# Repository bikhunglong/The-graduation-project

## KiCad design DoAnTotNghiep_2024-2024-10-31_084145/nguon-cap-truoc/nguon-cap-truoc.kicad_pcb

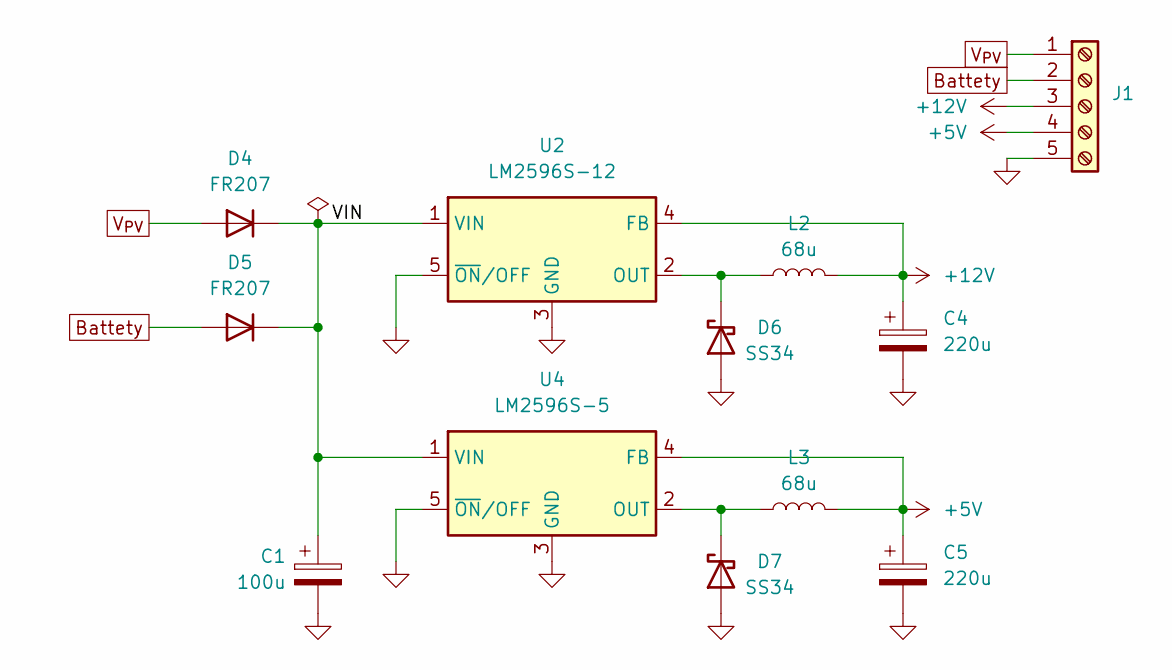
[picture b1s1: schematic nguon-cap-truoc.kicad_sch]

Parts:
C1: 100u; CP_Elec_6.3x5.4
C4, C5: 220u; CP_Elec_6.3x5.4
D4, D5: FR207; D_SMA
D6, D7: SS34; D_SMA
J1: Screw_Terminal_01x05; PinHeader_1x05_P2.54mm_Horizontal
L2, L3: 68u; L_12x12mm_H8mm
U2: LM2596S-12; TO-263-5_TabPin3
U4: LM2596S-5; TO-263-5_TabPin3

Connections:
+5V: C5.1, J1.4, L3.2, U4.4 (FB)
+12V: C4.1, J1.3, L2.2, U2.4 (FB)
/VIN: C1.1, D4.1 (K), D5.1 (K), U2.1 (VIN), U4.1 (VIN)
Battety: D5.2 (A), J1.2
GND: C1.2, C4.2, C5.2, D6.2 (A), D7.2 (A), J1.5, U2.3 (GND), U2.5 (~ON/OFF), U4.3 (GND), U4.5 (~ON/OFF)
unnamed: D6.1 (K), L2.1, U2.2 (OUT)
unnamed: D7.1 (K), L3.1, U4.2 (OUT)
V_{PV}: D4.2 (A), J1.1

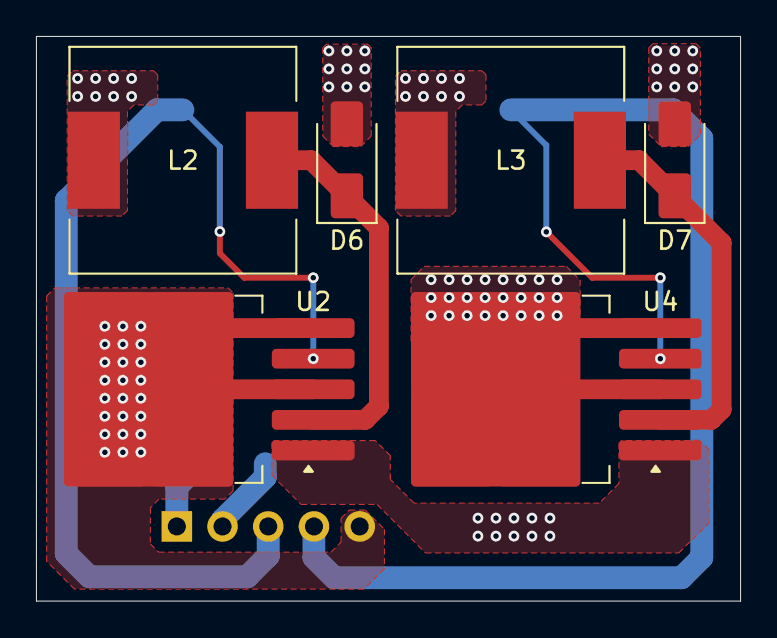
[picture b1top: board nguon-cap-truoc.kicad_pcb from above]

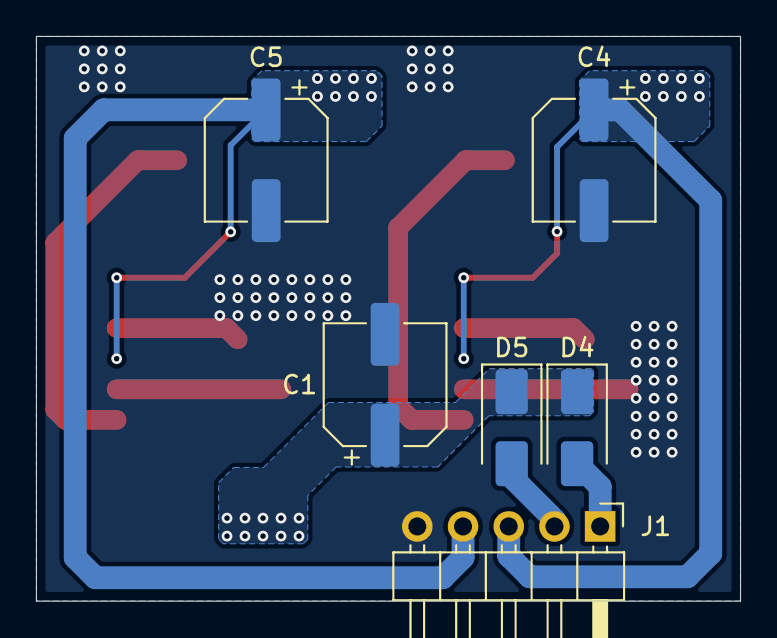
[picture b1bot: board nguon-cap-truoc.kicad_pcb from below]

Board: 2 copper layers, 39.1 x 31.4 mm, 12 parts (6 on the bottom side), 8 nets.

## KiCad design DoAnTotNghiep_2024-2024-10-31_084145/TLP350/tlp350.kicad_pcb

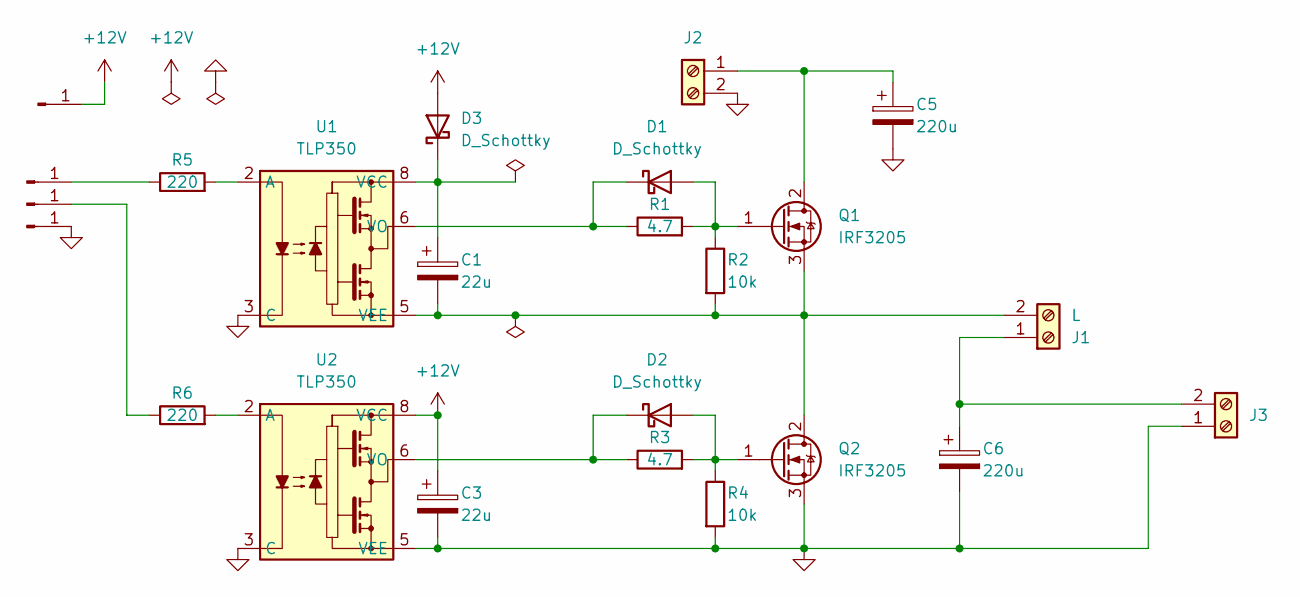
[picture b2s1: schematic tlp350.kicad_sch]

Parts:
C1, C3: 22u; CP_Radial_Tantal_D5.5mm_P5.00mm
C5, C6: 220u; CP_Radial_D10.0mm_P3.50mm
D1, D2, D3: D_Schottky; D_DO-41_SOD81_P10.16mm_Horizontal
J1, J3: L; TerminalBlock_Phoenix_MKDS-1,5-2-5.08_1x02_P5.08mm_Horizont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
J2: Screw_Terminal_01x02; TerminalBlock_Phoenix_MKDS-1,5-2-5.08_1x02_P5.08mm_Horizont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
J4, J5, J6, J7: Conn_01x01_Pin; Pin_D1.0mm_L10.0mm_LooseFit
Q1, Q2: IRF3205; TO-220-3_Vertical
R1, R3: 4.7; R_Axial_DIN0207_L6.3mm_D2.5mm_P10.16mm_Horizontal
R2, R4: 10k; R_Axial_DIN0207_L6.3mm_D2.5mm_P10.16mm_Horizontal
R5, R6: 220; R_Axial_DIN0207_L6.3mm_D2.5mm_P10.16mm_Horizontal
U1, U2: TLP350; DIP-8_W7.62mm

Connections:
+12V: C3.1, D3.2 (A), J7.1, U2.8 (VCC)
GND: C3.2, C5.2, C6.2, J2.2, J3.1, J6.1, Q2.3 (S), R4.2, U1.3 (C), U2.3 (C), U2.5 (VEE)
unnamed: D1.2 (A), Q1.1 (G), R1.2, R2.1
unnamed: D1.1 (K), R1.1, U1.6 (VO)
unnamed: D2.2 (A), Q2.1 (G), R3.2, R4.1
unnamed: D2.1 (K), R3.1, U2.6 (VO)
unnamed: C1.1, D3.1 (K), U1.8 (VCC)
unnamed: C6.1, J1.1, J3.2
unnamed: C1.2, J1.2, Q1.3 (S), Q2.2 (D), R2.2, U1.5 (VEE)
unnamed: C5.1, J2.1, Q1.2 (D)
unnamed: J4.1, R5.1
unnamed: J5.1, R6.1
unnamed: R5.2, U1.2 (A)
unnamed: R6.2, U2.2 (A)

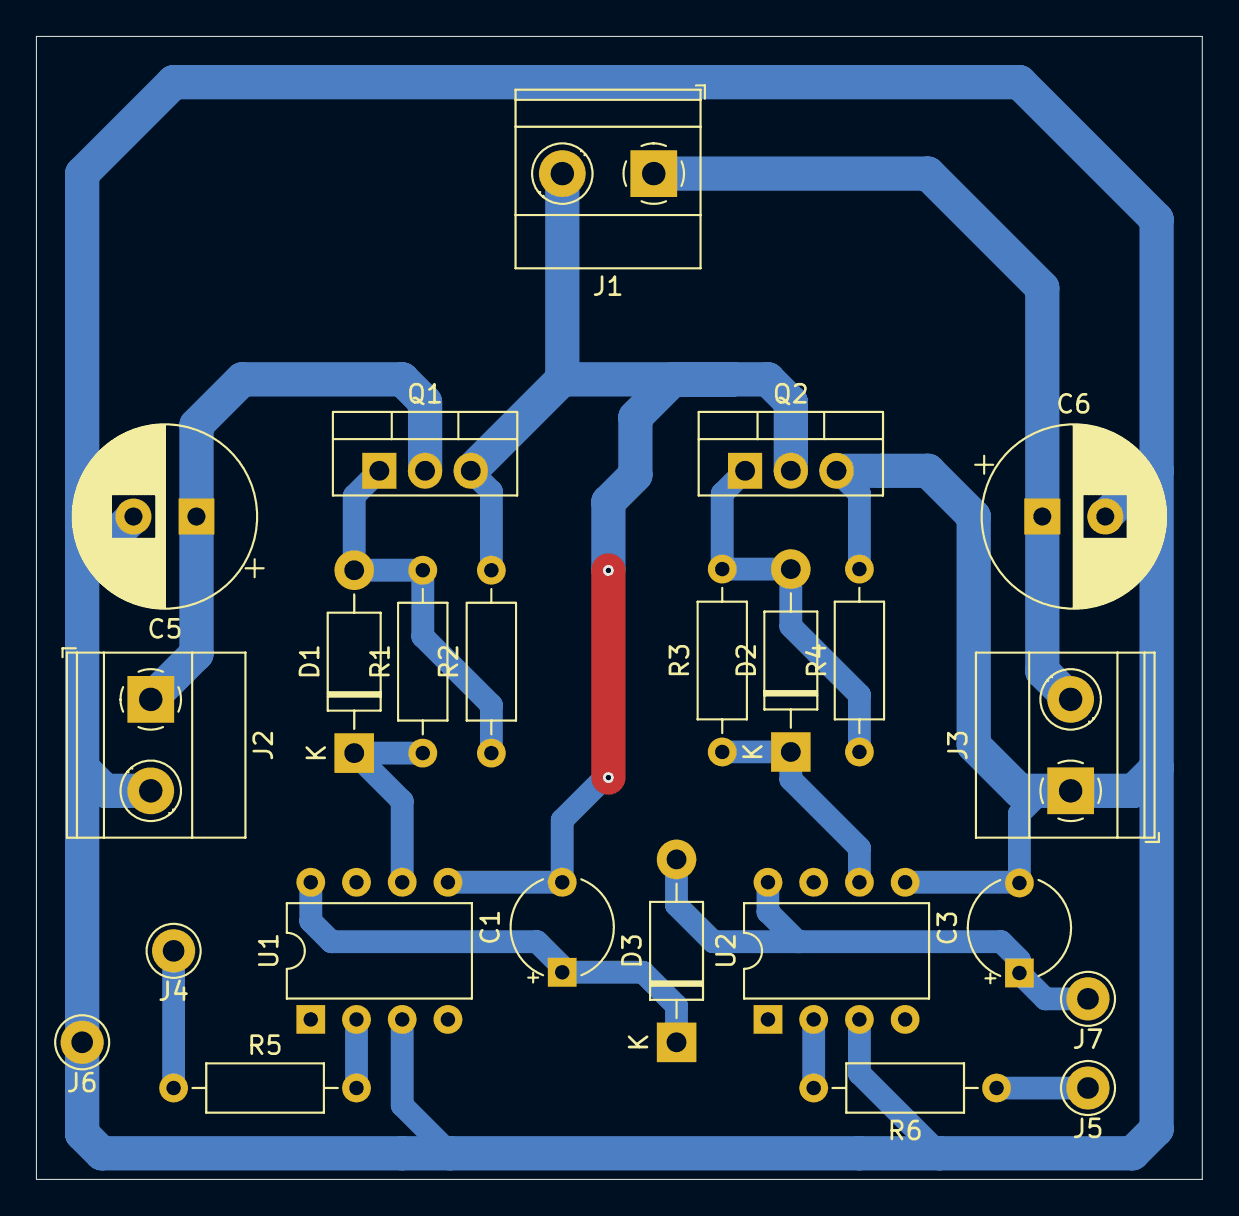
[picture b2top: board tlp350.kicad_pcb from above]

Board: 2 copper layers, 64.8 x 63.5 mm, 24 parts (0 on the bottom side), 14 nets.

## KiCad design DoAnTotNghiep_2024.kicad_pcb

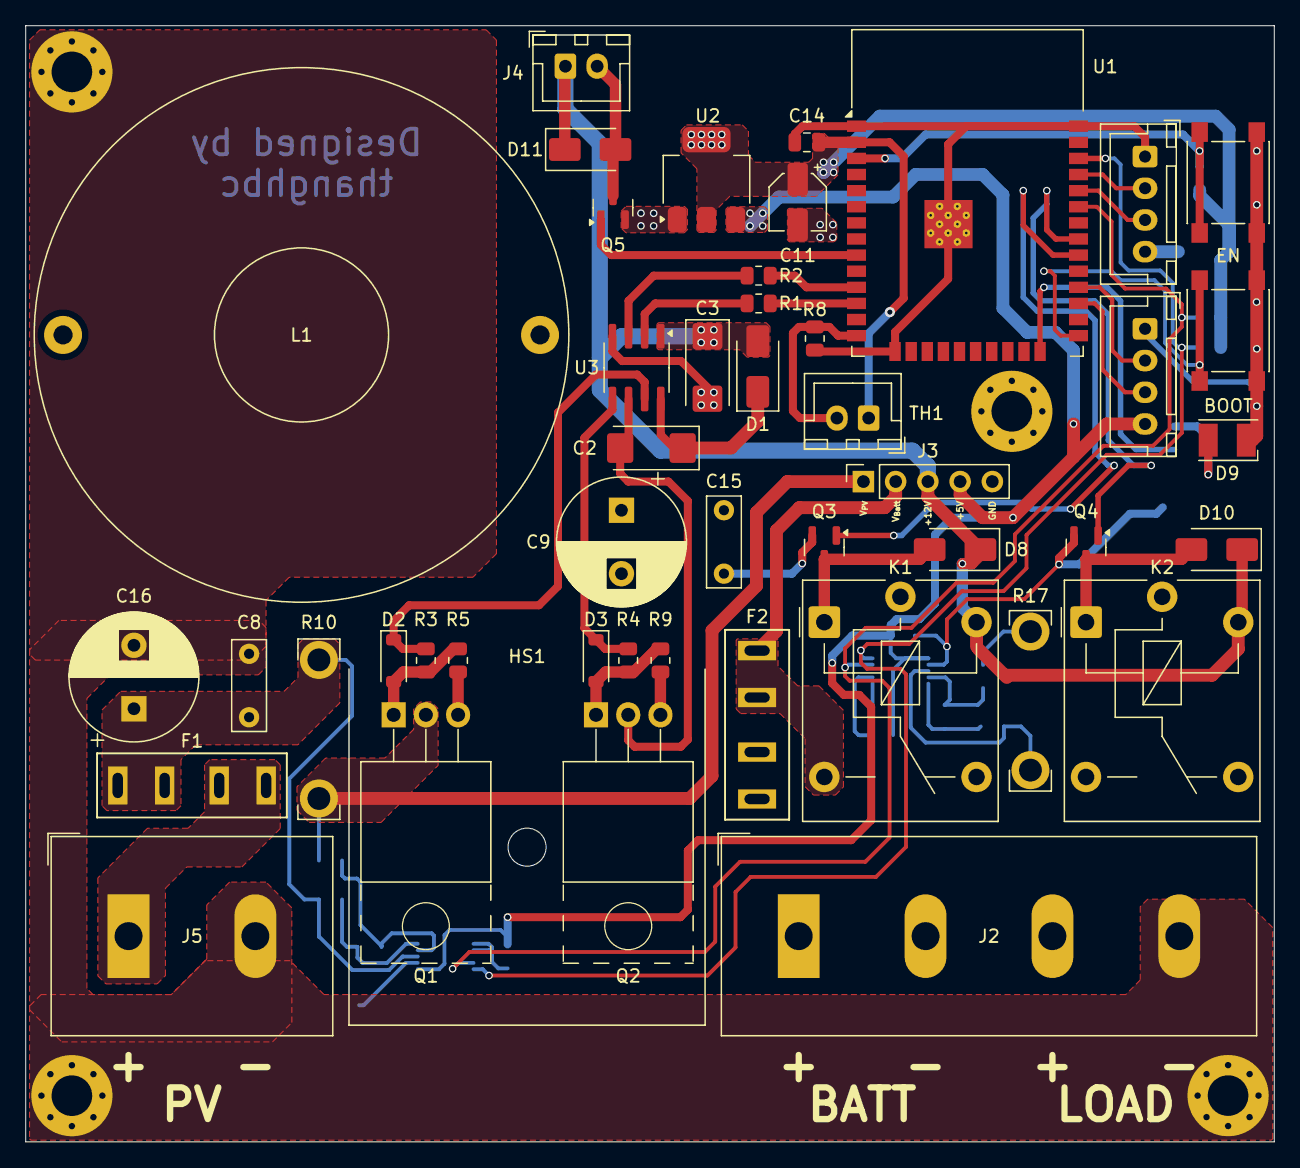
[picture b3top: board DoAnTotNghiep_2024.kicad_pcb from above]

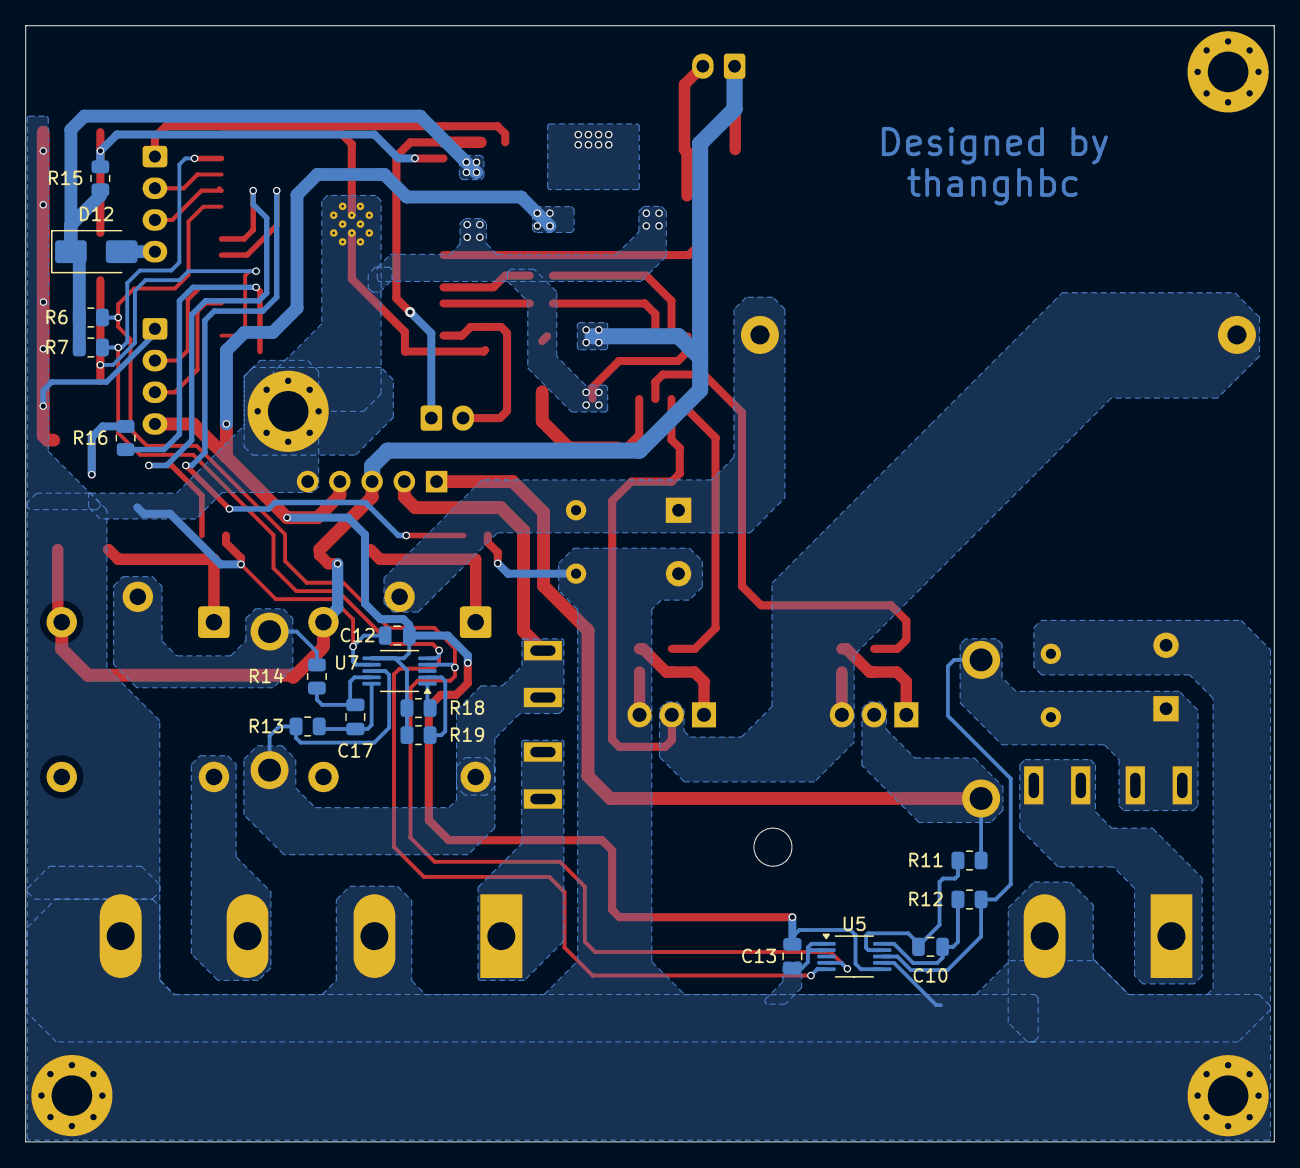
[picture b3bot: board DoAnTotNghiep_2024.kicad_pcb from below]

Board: 2 copper layers, 98.4 x 88.0 mm, 68 parts (17 on the bottom side), 46 nets.

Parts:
C2, C3: 22u; CP_EIA-6032-15_Kemet-U
C8, C15: 10n; C_Rect_L7.0mm_W2.5mm_P5.00mm
C9, C16: 220u; CP_Radial_D10.0mm_P5.00mm
C10, C12, C13, C14, C17: 10n; C_0805_2012Metric
C11: 4u7; CP_Elec_4x5.4
D1: SS34; D_SMA
D2, D3: SS14; D_SOD-123
D8, D10, D11, D12: SS14; D_SMA
D9: LED; LED_PLCC-2_3.4x3.0mm_KA
F1, F2: Fuse; fuseholder_car
H1, H2, H3, H4: MountingHole; MountingHole_3.2mm_M3_Pad_Via
HS1: Heatsink; Heatsink_28x28mm
J1: HMI Nextion; JST_XH_B4B-XH-A_1x04_P2.50mm_Vertical
J2: Screw_Terminal_01x04; TerminalBlock_Dinkle_DT-55-B01X-04_P10.00mm
J3: Screw_Terminal_01x05; PinSocket_1x05_P2.54mm_Vertical
J4: FAN; JST_XH_B2B-XH-A_1x02_P2.50mm_Vertical
J5: PV; TerminalBlock_Dinkle_DT-55-B01X-02_P10.00mm
J6: UPLOAD; JST_XH_B4B-XH-A_1x04_P2.50mm_Vertical
K1, K2: Relay_SPDT; Relay_SPDT_Finder_36.11
L1: L; L_Toroid_Horizontal_D41.9mm_P37.60mm_Vishay_TJ7
Q1, Q2: CSD19505; TO-220-3_Horizontal_TabUp
Q3, Q4, Q5: SS8050; SOT-23
R1, R2, R16: 150; R_0805_2012Metric
R3, R4, R11, R12, R13, R14: 4.7; R_0805_2012Metric
R5, R8, R9, R15: 10k; R_0805_2012Metric
R6, R7, R18, R19: 2k4; R_0805_2012Metric
R10, R17: 10m; R-shunt
SW1: EN; SW_Push_1P1T_NO_6x6mm_H9.5mm
SW2: BOOT; SW_Push_1P1T_NO_6x6mm_H9.5mm
TH1: 10k; JST_XH_B2B-XH-A_1x02_P2.50mm_Vertical
U1: ESP32-WROOM-32U; ESP32-WROOM-32D
U2: LM1117MP-3.3; SOT-223-3_TabPin2
U3: IR2104; SOIC-8_3.9x4.9mm_P1.27mm
U5, U7: INA226; VSSOP-10_3x3mm_P0.5mm

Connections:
+3.3V: C11.1, C14.1, D12.1 (K), R6.1, R7.1, R15.1, TH1.1, U1.2 (VDD), U2.2 (VO)
+5V: C12.1, C13.1, J1.4, J3.4, R18.1, R19.1, U2.3 (VI), U5.6 (VS), U7.6 (VS)
+12V: C3.1, D1.2 (A), D8.1 (K), D10.1 (K), D11.1 (K), J3.3, J4.1, K1.A2, K2.A2, U3.1 (VCC)
BATT_PIN: F2.1, J2.1
BOOT: SW2.2, U1.25 (IO0)
Battety: F2.2, J3.2, K1.14, R13.1, R17.1, U7.8 (Vbus)
EN: R15.2, SW1.2, U1.3 (EN)
Enable Batt: Q3.1 (B), U1.30 (IO18)
Enable Load: Q4.1 (B), U1.31 (IO19)
FAN: Q5.1 (B), U1.9 (IO33)
GND: C3.2, C8.2, C9.2, C11.2, C12.2, C13.2, C14.2, C15.2, C16.2, D9.1 (K), H1.1, H2.1, H3.1, H4.1, J1.1, J2.2, J2.4, J3.5, J5.2, J6.1, Q2.3 (S), Q3.2 (E), Q4.2 (E), Q5.2 (E), R8.2, R9.2, SW1.1, SW2.1, U1.1 (GND), U1.15 (GND), U1.38 (GND), U1.39 (GND), U2.1 (GND), U3.4 (COM), U5.1 (A1), U5.2 (A0), U5.7 (GND), U7.7 (GND)
HMI_{RX}: J1.2, U1.28 (IO17)
HMI_{TX}: J1.3, U1.27 (IO16)
LED: R16.1, U1.24 (IO2)
LOAD_PIN: J2.3, K2.14
unnamed: C9.1, C15.1, K1.11, L1.2
unnamed: C2.1, D1.1 (K), U3.8 (VB)
unnamed: D2.2 (A), Q1.1 (G), R3.2, R5.1
unnamed: D2.1 (K), R3.1, U3.7 (HO)
unnamed: D3.2 (A), Q2.1 (G), R4.2, R9.1
unnamed: D3.1 (K), R4.1, U3.5 (LO)
unnamed: D8.2 (A), K1.A1, Q3.3 (C)
unnamed: D9.2 (A), R16.2
unnamed: D10.2 (A), K2.A1, Q4.3 (C)
unnamed: D11.2 (A), J4.2, Q5.3 (C)
unnamed: D12.2 (A), J6.4
unnamed: F1.1, J5.1
unnamed: K2.11, R14.1, R17.2
unnamed: C2.2, L1.1, Q1.3 (S), Q2.2 (D), R5.2, U3.6 (VS)
unnamed: R1.2, U3.2 (IN)
unnamed: R2.1, U3.3 (~SD)
unnamed: C8.1, C16.1, F1.2, R10.1, R12.1, U5.8 (Vbus)
unnamed: C10.1, R12.2, U5.10 (Vin+)
unnamed: C10.2, R11.2, U5.9 (Vin-)
unnamed: R19.2, U7.2 (A0)
unnamed: R18.2, U7.1 (A1)
unnamed: C17.1, R13.2, U7.10 (Vin+)
unnamed: C17.2, R14.2, U7.9 (Vin-)
PWM: R1.1, U1.12 (IO27)
RX: J6.2, U1.35 (TXD0/IO1)
RXD0: J6.3, U1.34 (RXD0/IO3)
SCL: R7.2, U1.36 (IO22), U5.5 (SCL), U7.5 (SCL)
SDA: R6.2, U1.33 (IO21), U5.4 (SDA), U7.4 (SDA)
SHUTDOWN: R2.2, U1.11 (IO26)
Temp: R8.1, TH1.2, U1.14 (IO12)
V_{PV}: J3.1, Q1.2 (D), R10.2, R11.1
